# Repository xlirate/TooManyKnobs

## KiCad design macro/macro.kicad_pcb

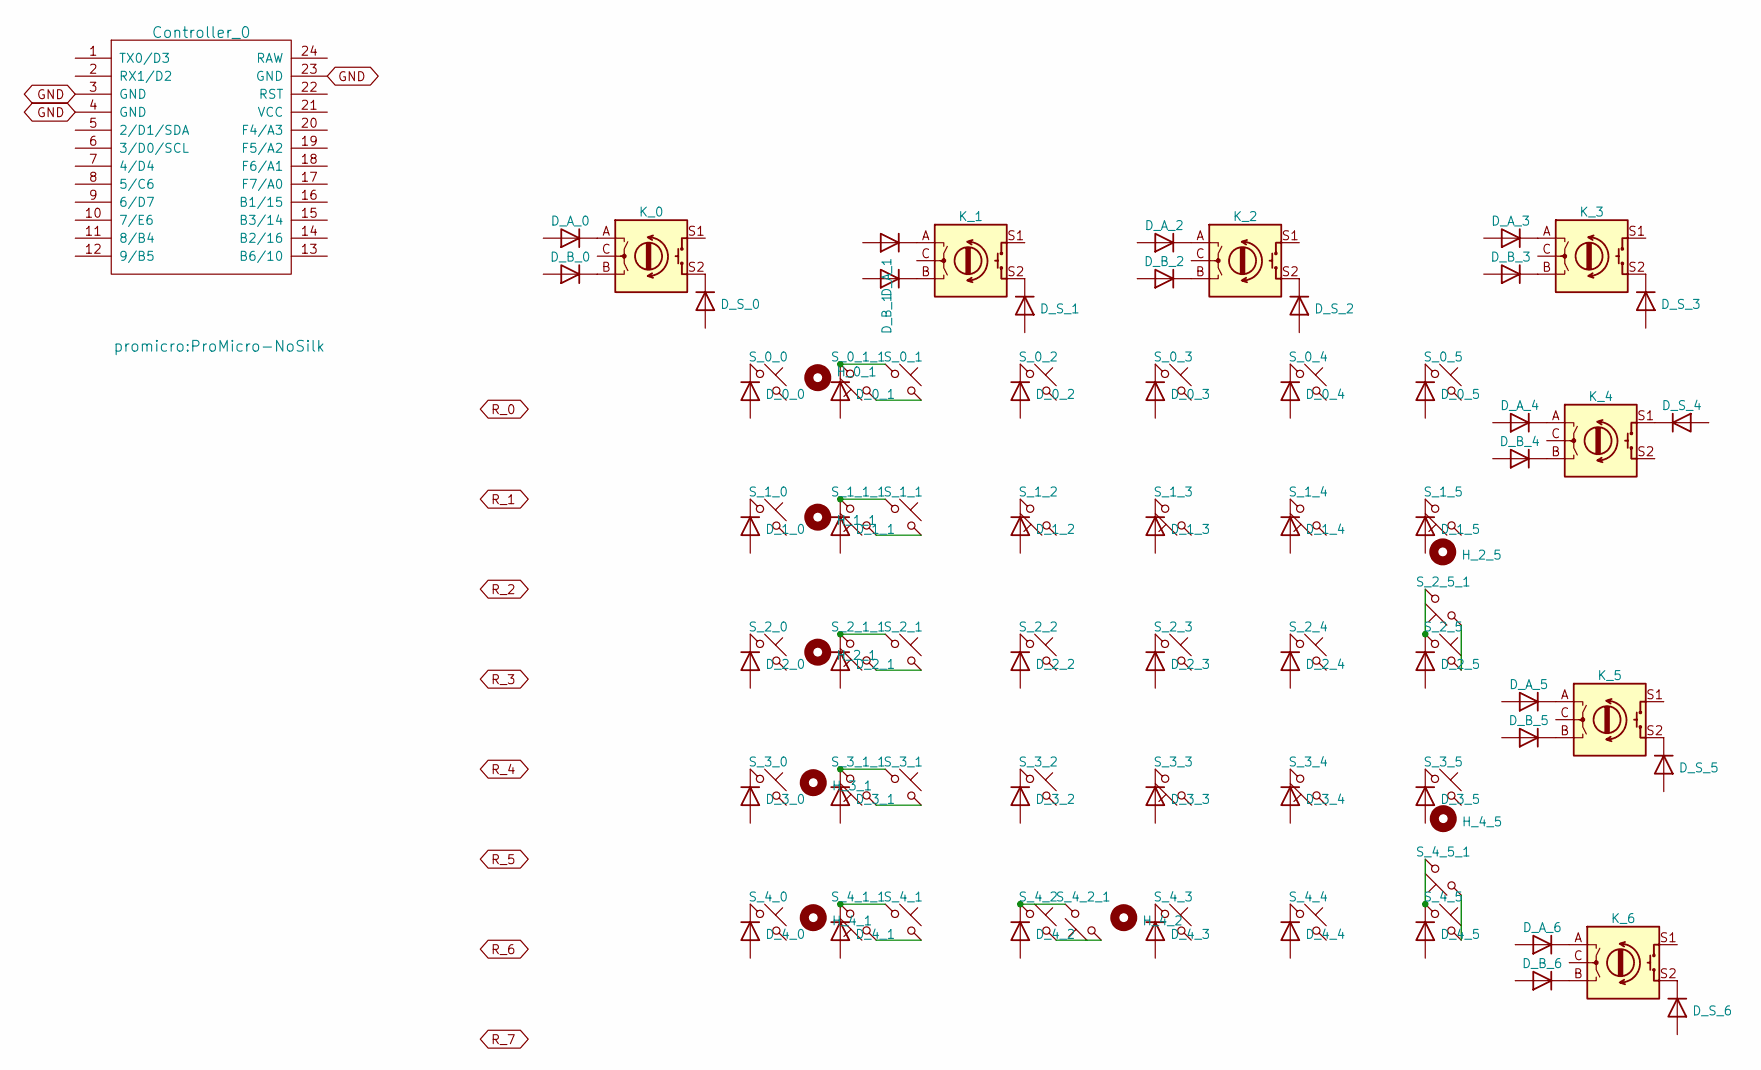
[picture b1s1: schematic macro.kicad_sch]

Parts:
Controller_0: ProMicro; ProMicro-NoSilk
D_0_0, D_0_1, D_0_2, D_0_3, D_0_4, D_0_5, D_1_0, D_1_1, D_1_2, D_1_3, D_1_4, D_1_5, D_2_0, D_2_1, D_2_2, D_2_3, D_2_4, D_2_5, D_3_0, D_3_1, D_3_2, D_3_3, D_3_4, D_3_5, D_4_0, D_4_1, D_4_2, D_4_3, D_4_4, D_4_5: D; D3_TH_SMD_v2
D_A_0, D_A_1, D_A_2, D_A_3, D_A_4, D_A_5, D_A_6: D; D3_TH_SMD_v2
D_B_0, D_B_1, D_B_2, D_B_3, D_B_4, D_B_5, D_B_6: D; D3_TH_SMD_v2
D_S_0, D_S_1, D_S_2, D_S_3, D_S_4, D_S_5, D_S_6: D; D3_TH_SMD_v2
H_0_1, H_1_1, H_2_1, H_2_5, H_3_1, H_4_1, H_4_2, H_4_5: MountingHole; MXOnly-2U-NoSwitch
K_0, K_1, K_2, K_3, K_4, K_5, K_6: RotaryEncoder_Switch; RotaryEncoder_Alps_EC11E-Switch_Vertical_H20mm
S_0_0, S_0_1, S_0_1_1, S_0_2, S_0_3, S_0_4, S_0_5, S_1_0, S_1_1, S_1_1_1, S_1_2, S_1_3, S_1_4, S_1_5, S_2_0, S_2_1, S_2_1_1, S_2_2, S_2_3, S_2_4, S_2_5, S_2_5_1, S_3_0, S_3_1, S_3_1_1, S_3_2, S_3_3, S_3_4, S_3_5, S_4_0, S_4_1, S_4_1_1, S_4_2, S_4_2_1, S_4_3, S_4_4, S_4_5, S_4_5_1: SW_Push_45deg; MXOnly-1U-NoLED

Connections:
GND: Controller_0.3 (GND), Controller_0.4 (GND), Controller_0.23 (GND)
unnamed: D_1_3.1 (K), S_1_3.2
unnamed: D_1_4.1 (K), S_1_4.2
unnamed: D_1_5.1 (K), S_1_5.2
unnamed: D_3_3.1 (K), S_3_3.2
unnamed: D_3_4.1 (K), S_3_4.2
unnamed: D_3_5.1 (K), S_3_5.1
unnamed: D_A_4.1 (K), K_4.A
unnamed: D_S_4.1 (K), K_4.S1
unnamed: D_A_0.1 (K), K_0.A
unnamed: D_B_0.1 (K), K_0.B
unnamed: D_S_0.1 (K), K_0.S2
unnamed: D_A_1.1 (K), K_1.A
unnamed: D_B_1.1 (K), K_1.B
unnamed: D_S_1.1 (K), K_1.S2
unnamed: D_A_2.1 (K), K_2.A
unnamed: D_B_2.1 (K), K_2.B
unnamed: D_S_2.1 (K), K_2.S2
unnamed: D_A_3.1 (K), K_3.A
unnamed: D_B_3.1 (K), K_3.B
unnamed: D_S_3.1 (K), K_3.S2
unnamed: D_B_4.1 (K), K_4.B
unnamed: D_A_5.1 (K), K_5.A
unnamed: D_B_5.1 (K), K_5.B
unnamed: D_S_5.1 (K), K_5.S2
unnamed: D_A_6.1 (K), K_6.A
unnamed: D_B_6.1 (K), K_6.B
unnamed: D_S_6.1 (K), K_6.S2
unnamed: D_0_0.1 (K), S_0_0.1
unnamed: D_0_1.1 (K), S_0_1.1, S_0_1_1.2
unnamed: S_0_1.2, S_0_1_1.1
unnamed: D_0_2.1 (K), S_0_2.1
unnamed: D_0_3.1 (K), S_0_3.1
unnamed: D_0_4.1 (K), S_0_4.1
unnamed: D_0_5.1 (K), S_0_5.1
unnamed: D_1_0.1 (K), S_1_0.1
unnamed: D_1_1.1 (K), S_1_1.1, S_1_1_1.2
unnamed: S_1_1.2, S_1_1_1.1
unnamed: D_1_2.1 (K), S_1_2.2
unnamed: D_2_0.1 (K), S_2_0.1
unnamed: D_2_1.1 (K), S_2_1.1, S_2_1_1.2
unnamed: S_2_1.2, S_2_1_1.1
unnamed: D_2_2.1 (K), S_2_2.1
unnamed: D_2_3.1 (K), S_2_3.1
unnamed: D_2_4.1 (K), S_2_4.1
unnamed: D_2_5.1 (K), S_2_5.1, S_2_5_1.2
unnamed: S_2_5.2, S_2_5_1.1
unnamed: D_3_0.1 (K), S_3_0.1
unnamed: D_3_1.1 (K), S_3_1.1, S_3_1_1.2
unnamed: S_3_1.2, S_3_1_1.1
unnamed: D_3_2.1 (K), S_3_2.1
unnamed: D_4_0.1 (K), S_4_0.1
unnamed: D_4_1.1 (K), S_4_1.1, S_4_1_1.2
unnamed: S_4_1.2, S_4_1_1.1
unnamed: D_4_2.1 (K), S_4_2.1, S_4_2_1.2
unnamed: S_4_2.2, S_4_2_1.1
unnamed: D_4_3.1 (K), S_4_3.1
unnamed: D_4_4.1 (K), S_4_4.1
unnamed: D_4_5.1 (K), S_4_5.1, S_4_5_1.2
unnamed: S_4_5.2, S_4_5_1.1

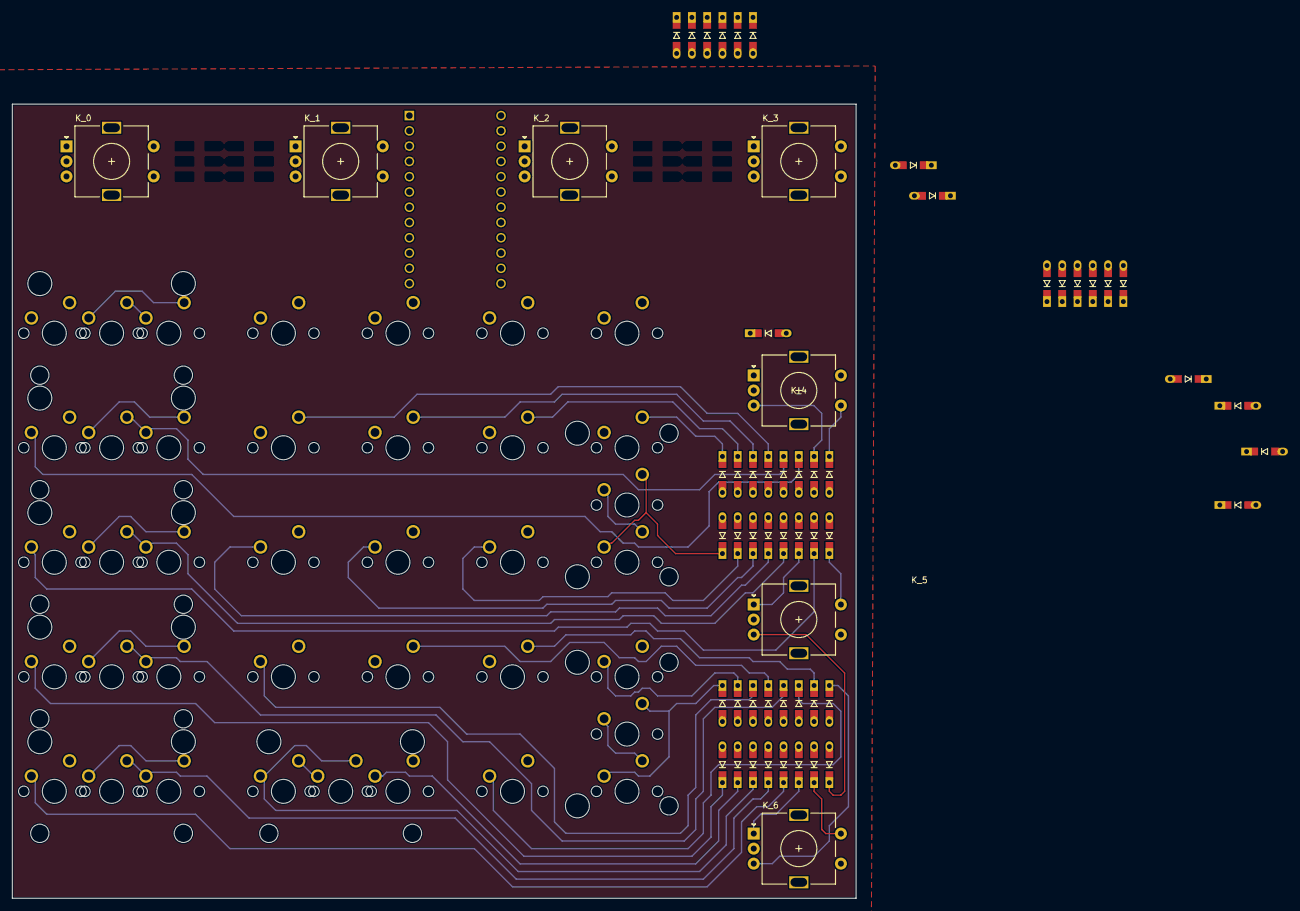
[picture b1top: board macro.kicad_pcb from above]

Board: 2 copper layers, 140.3 x 132.1 mm, 105 parts (0 on the bottom side), 60 nets.

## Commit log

2022-08-27 added parts submodules
2023-01-03 some stuff
